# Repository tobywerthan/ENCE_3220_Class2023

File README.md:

# **ENCE_3220_Class2023 Phase D**
Phase D of ENCE-3220 tasked students to design a PCB using the STM32f407G and the STM32CubeIDE. A friend of mine recently asked me if I could design a device that would help him monitor the temperature in his bearded dragon's enclosure. This project seemed like the perfect opportunity to begin designing such a device.

## Project Requirements
The requirements for this temperature monitor aren't complex. The system must be able to read the current temperature, additional data is a plus. The system must also be able to display that data in a readable manner. The system must utilize the STM32F407G Discovery Board, and the software must be developed in the STM32CubeIDE. In summary, the system requirements are as follows: 
- Read temperature
- Display temperature in real time
- Utilize the STM32F407G Discovery Board
- Software developed in the STM32CubeIDE

## System Design
The design for this system includes the STM32F407G Discovery Board, an lcd display, and a temperature sensor. A block diagram of key components and their pin connections to the STM32F4. 

## Components Selection
Key components for this system include the LCD1602A display, the DHT11 temperature and humidity sensor, and the STM32F4 discovery board. A full list of the required components can be seen in the table below. 

| References  | Value       | Footprint   |
| :-----------: | :-----------: | :-----------: |
| U2 | DHT11 | Connector_PinSocket_2.54mm:PinSocket_1x03_P2.54mm_Vertical_SMD_Pin1Right |
| U1 | LCD1602A | Connector_PinSocket_2.54mm:PinSocket_1x16_P2.54mm_Vertical_SMD_Pin1Right |
| J1 & J2 | STM32F4 Discovery Board | 2x Connector_PinSocket_2.54mm:PinSocket_2x25_P2.54mm_Vertical |
| RV1 | 1000Ω | Connector_PinSocket_2.54mm:PinSocket_1x05_P2.54mm_Vertical_SMD_Pin1Right |
| R1 | 910Ω | Resistor_SMD:R_0603_1608Metric |
| C1 | 1mF | Capacitor_SMD:C_0603_1608Metric |

## Build Prototype

## STM32 Shield Design
The goal for this project was to develop a shield for the STM32F4 that implements the designed system. 

### Schematic
The schematic for this system contains three modules. The modules are categorized by component: "LCD1602A Pinout", "DHT11 Pinout", and "STM32 Discovery board Pinout". 

#### LCD Display

#### DHT11

#### STM32F4

### PCB
This shield was designed so that the componenets used during prototyping could be directly placed on the PCB using pin socket connectors instead of surface mounting components. The main concern when designing the PCB was to allocate enough space for the components once they are connected to the pin sockets. This was managed through some crude measurements as well as trial and error. 

#### KiCad

#### 3D Render

#### 3D Render with Components 

## Software Development
Both the LCD display and the temperature sensor require delays in units of microseconds in order to function correctly. Unfortunately, the delay provided by the HAL library has a minimum of 1 millisecond. To achieve a delay in microseconds, the following code is implemented in the library for both sensors:
```
void microDelay (uint16_t us)
{
	__HAL_TIM_SET_COUNTER(&timer, 0);
	while (__HAL_TIM_GET_COUNTER(&timer) < us);
}
```
The timers used for the micro delays are timer1 and timer2 sourced by the internal clock of the STM32. Both timers share a prescaler value of 83 and a counter period of 4095. The LCD library provided functions for clearing the display, moving the cursor on the display, and writing strings to the display. Every loop execution, the LCD displays the temperature on the top row, and then the humidity on the bottom row. The LCD needs to clear every loop execution as the values update, this forces the loop to implement a delay so that the value can display befor being cleared. Because the LCD displays requires a delay, the rate at which the temperature sensor is read needs to be faster than that delay. In this case, the delay for the lcd was 1 second. Therefore, a timer driven interrupt is implemented using timer6. This interrupt occurs every half second, which is plenty fast enough considering the display rate of the LCD display. Each time the interrupt occurs, the temperature and humidity values are read and stored. A flow chart of the program can be seen below:

## Future Iterations

While this project is practical, this kind of device already exists. A way to improve this design would be to use the ESP8266 microchip to send alerts to a certain device once the temperature has reached a specified threshold. Additionally, adding a UVB sensor would give the user more information about the enviornment. Powering the system with a battery would allow it to be portable. Because the device is meant to detect high temperatures and UVB, charging the battery through solar might not be a bad idea either.

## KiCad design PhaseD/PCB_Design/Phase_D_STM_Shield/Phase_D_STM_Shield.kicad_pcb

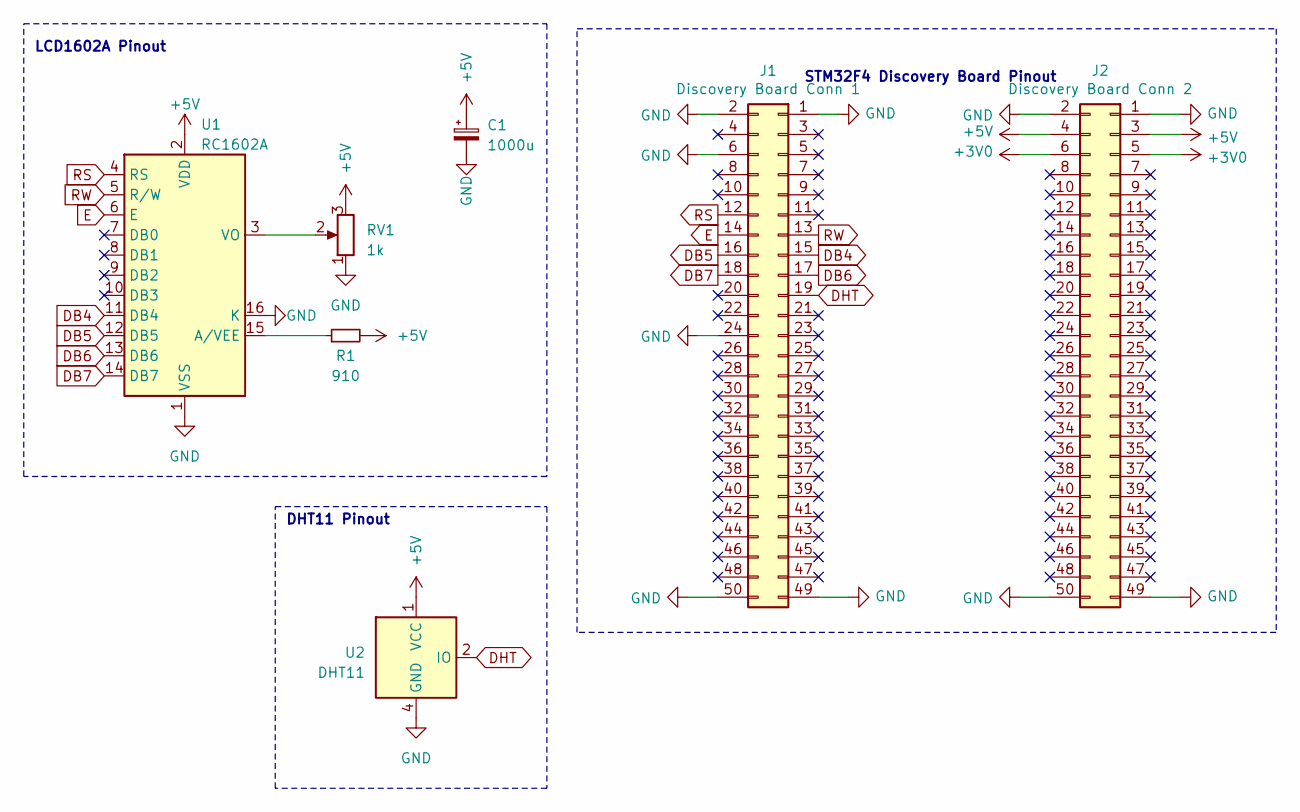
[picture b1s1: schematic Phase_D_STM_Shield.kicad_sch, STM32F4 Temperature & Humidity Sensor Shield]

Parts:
C1: 1000u; C_0603_1608Metric
J1: Discovery Board Conn 1; PinSocket_2x25_P2.54mm_Vertical
J2: Discovery Board Conn 2; PinSocket_2x25_P2.54mm_Vertical
R1: 910; R_0603_1608Metric
RV1: 1k; PinSocket_1x05_P2.54mm_Vertical_SMD_Pin1Right
U1: RC1602A; PinSocket_1x16_P2.54mm_Vertical_SMD_Pin1Right
U2: DHT11; PinSocket_1x03_P2.54mm_Vertical_SMD_Pin1Right

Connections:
+3V0: J2.5, J2.6
+5V: C1.1, J2.3, J2.4, R1.2, RV1.3, U1.2 (VDD), U2.1 (VCC)
DB4: J1.15, U1.11 (DB4)
DB5: J1.16, U1.12 (DB5)
DB6: J1.17, U1.13 (DB6)
DB7: J1.18, U1.14 (DB7)
DHT: J1.19, U2.2 (IO)
E: J1.14, U1.6 (E)
GND: C1.2, J1.1, J1.2, J1.6, J1.24, J1.49, J1.50, J2.1, J2.2, J2.49, J2.50, RV1.1, U1.1 (VSS), U1.16 (K), U2.4 (GND)
unnamed: R1.1, U1.15 (A/VEE)
unnamed: RV1.2, U1.3 (VO)
RS: J1.12, U1.4 (RS)
RW: J1.13, U1.5 (R/W)

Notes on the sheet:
STM32F4 Discovery Board Pinout
DHT11 Pinout
LCD1602A Pinout

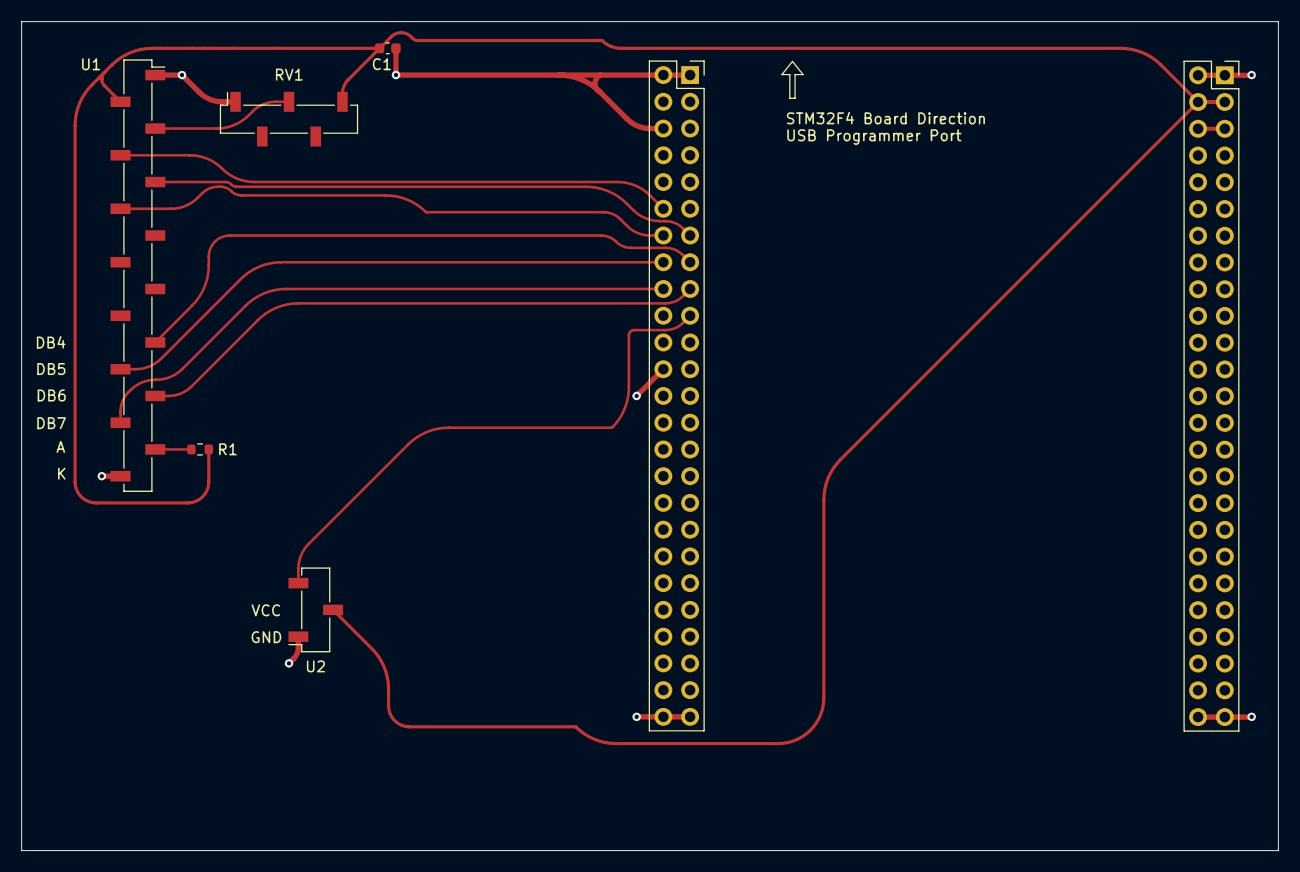
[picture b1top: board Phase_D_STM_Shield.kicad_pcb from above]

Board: 2 copper layers, 119.4 x 78.7 mm, 7 parts (0 on the bottom side), 13 nets.

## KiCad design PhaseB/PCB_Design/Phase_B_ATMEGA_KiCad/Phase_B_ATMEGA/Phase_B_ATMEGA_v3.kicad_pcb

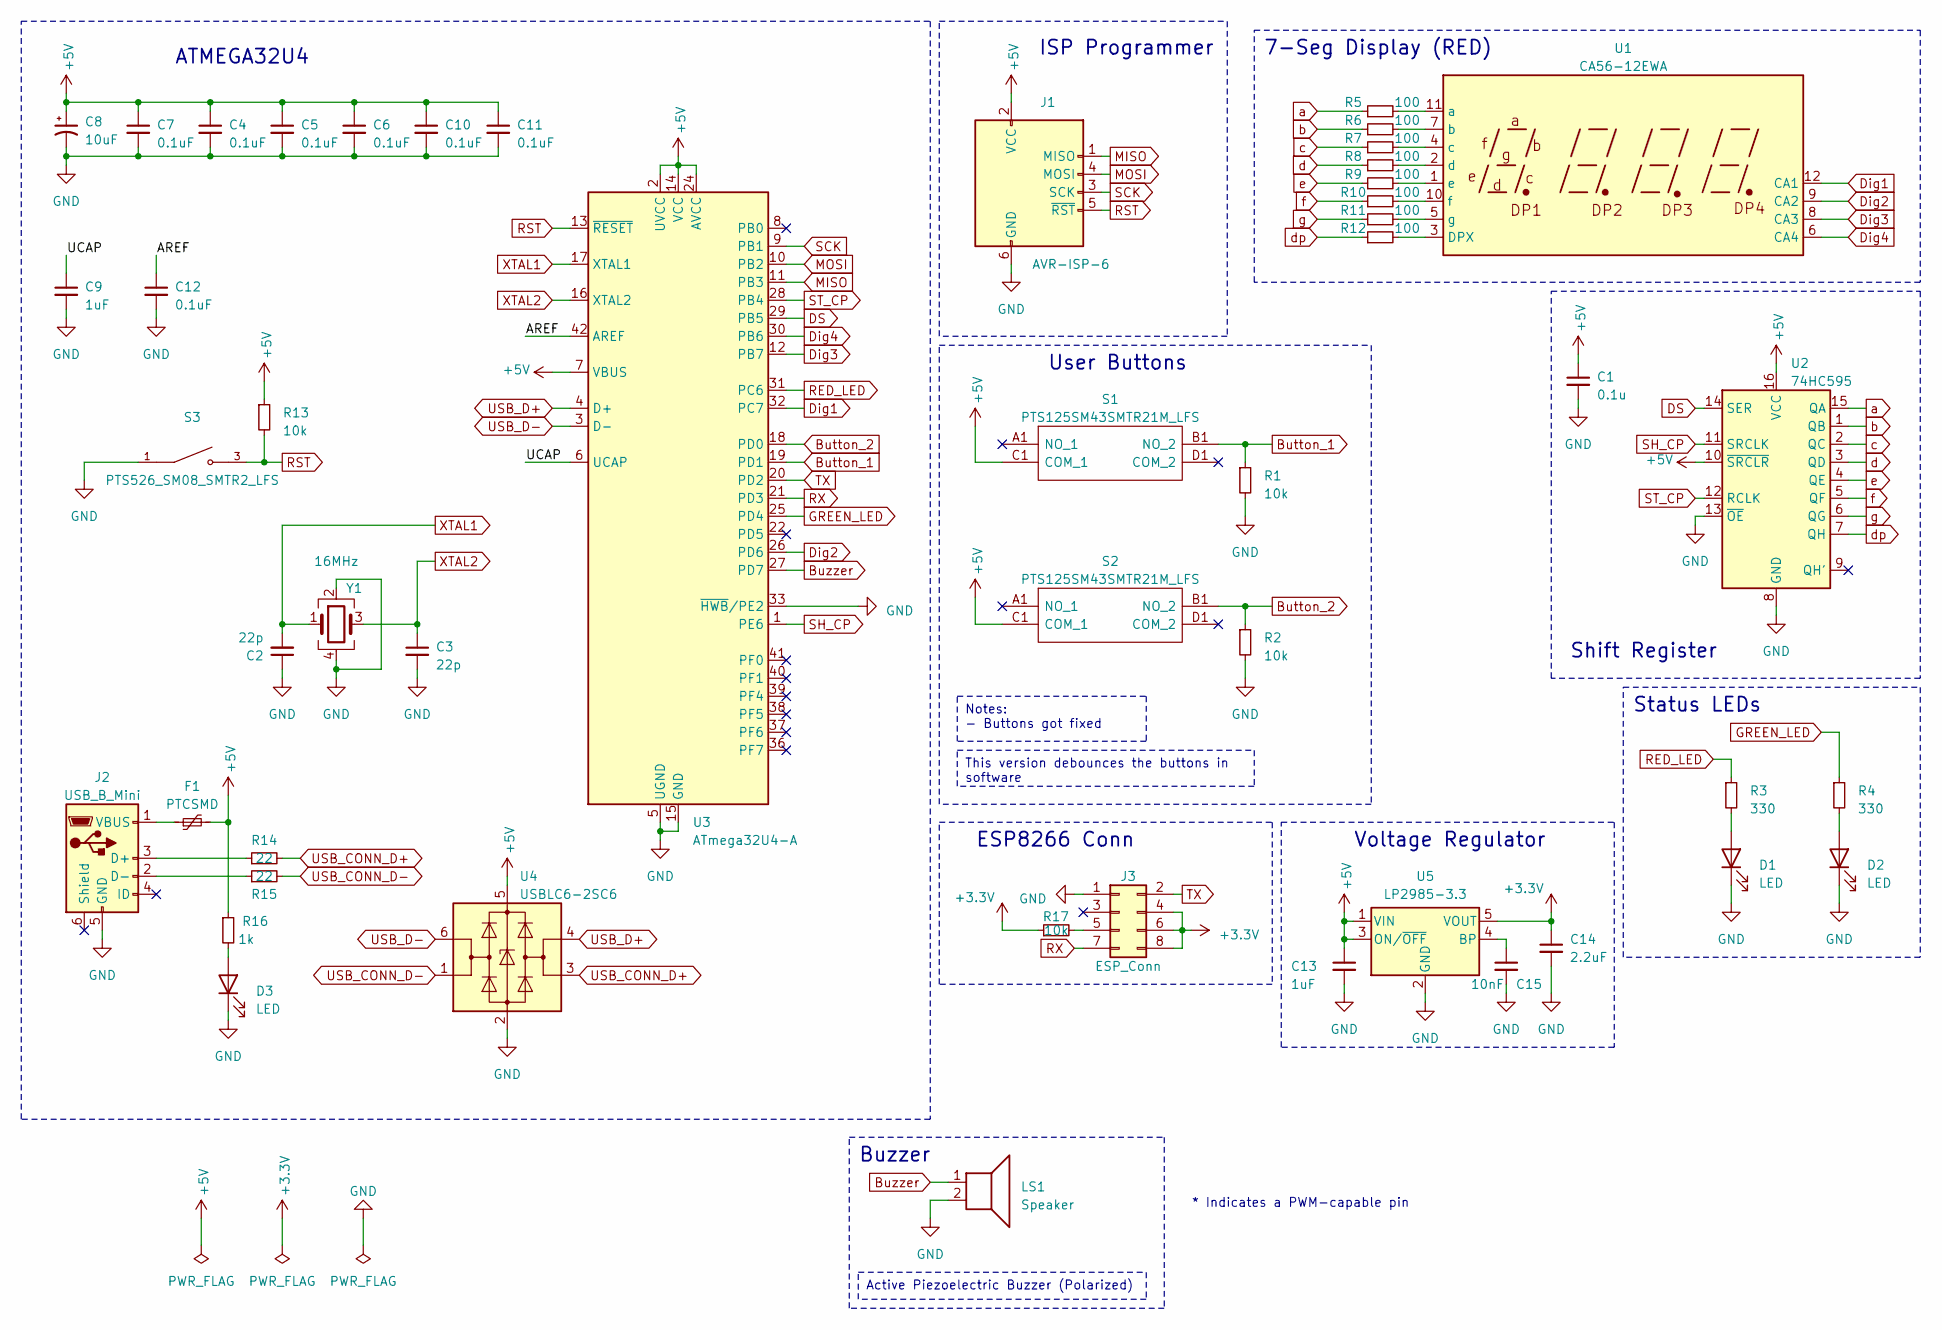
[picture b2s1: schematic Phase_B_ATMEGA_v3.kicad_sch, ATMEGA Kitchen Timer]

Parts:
C1: 0.1u; C_0603_1608Metric
C2, C3: 22p; C_0603_1608Metric
C4, C5, C6, C7, C10, C11, C12: 0.1uF; C_0603_1608Metric
C8: 10uF; C_0805_2012Metric
C9, C13: 1uF; C_0603_1608Metric
C14: 2.2uF; C_0603_1608Metric
C15: 10nF; C_0603_1608Metric
D1, D2, D3: LED; LED_0805_2012Metric
F1: PTCSMD; Fuse_1812_4532Metric
J1: AVR-ISP-6; PinSocket_2x03_P2.54mm_Vertical
J2: USB_B_Mini; USB_Mini-B_Lumberg_2486_01_Horizontal
J3: ESP_Conn; PinSocket_2x04_P2.54mm_Vertical
LS1: Speaker; Buzzer_12x9.5RM7.6
R1, R2: 10k; R_0805_2012Metric
R3, R4: 330; R_0805_2012Metric
R5, R6, R7, R8, R9, R10, R11, R12: 100; R_0805_2012Metric
R13, R17: 10k; R_0603_1608Metric
R14, R15: 22; R_0603_1608Metric
R16: 1k; R_0603_1608Metric
S1, S2: PTS125SM43SMTR21M_LFS; PTS125_SMD_Button; Manufacturer_Part_Number PTS125SM43SMTR21M LFS; Mouser Part Number 611-PTS125S43SMTRLFS
S3: PTS526_SM08_SMTR2_LFS; PTS526_SMD_Button; PARTREV 20 mar 19
U1: CA56-12EWA
U2: 74HC595; TSSOP-16_4.4x5mm_P0.65mm
U3: ATmega32U4-A; TQFP-44_10x10mm_P0.8mm
U4: USBLC6-2SC6; SOT-23-6
U5: LP2985-3.3; SOT-23-5
Y1: 16MHz; Crystal_SMD_Abracon_ABM8G-4Pin_3.2x2.5mm

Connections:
+3.3V: C14.1, J3.4, J3.6, J3.8, R17.1, U5.5 (VOUT)
+5V: C1.1, C4.1, C5.1, C6.1, C7.1, C8.1, C10.1, C11.1, C13.1, F1.2, J1.2 (VCC), R13.1, R16.1, S1.C1 (COM_1), S2.C1 (COM_1), U2.10 (~SRCLR), U2.16 (VCC), U3.2 (UVCC), U3.7 (VBUS), U3.14 (VCC), U3.24 (AVCC), U3.34 (VCC), U3.44 (AVCC), U4.5 (VBUS), U5.1 (VIN), U5.3 (ON/~OFF)
/AREF: C12.1, U3.42 (AREF)
/UCAP: C9.1, U3.6 (UCAP)
Button_1: R1.1, S1.B1 (NO_2), U3.19 (PD1)
Button_2: R2.1, S2.B1 (NO_2), U3.18 (PD0)
Buzzer: LS1.1, U3.27 (PD7)
DS: U2.14 (SER), U3.29 (PB5)
Dig1: U1.12 (CA1), U3.32 (PC7)
Dig2: U1.9 (CA2), U3.26 (PD6)
Dig3: U1.8 (CA3), U3.12 (PB7)
Dig4: U1.6 (CA4), U3.30 (PB6)
GND: C1.2, C2.1, C3.2, C4.2, C5.2, C6.2, C7.2, C8.2, C9.2, C10.2, C11.2, C12.2, C13.2, C14.2, C15.2, D1.1 (K), D2.1 (K), D3.1 (K), J1.6 (GND), J2.5 (GND), J3.1, LS1.2, R1.2, R2.2, S3.1, U2.8 (GND), U2.13 (~OE), U3.5 (UGND), U3.15 (GND), U3.23 (GND), U3.33 (~HWB/PE2), U3.35 (GND), U3.43 (GND), U4.2 (GND), U5.2 (GND), Y1.2, Y1.4
GREEN_LED: R4.1, U3.25 (PD4)
MISO: J1.1 (MISO), U3.11 (PB3)
MOSI: J1.4 (MOSI), U3.10 (PB2)
unnamed: D1.2 (A), R3.2
unnamed: D2.2 (A), R4.2
unnamed: D3.2 (A), R16.2
unnamed: J2.3 (D+), R14.1
unnamed: J2.2 (D-), R15.1
unnamed: F1.1, J2.1 (VBUS)
unnamed: J3.5, R17.2
unnamed: R12.2, U1.3 (DPX)
unnamed: R5.2, U1.11 (a)
unnamed: R6.2, U1.7 (b)
unnamed: R7.2, U1.4 (c)
unnamed: R8.2, U1.2 (d)
unnamed: R9.2, U1.1 (e)
unnamed: R10.2, U1.10 (f)
unnamed: R11.2, U1.5 (g)
unnamed: C15.1, U5.4 (BP)
RED_LED: R3.1, U3.31 (PC6)
RST: J1.5 (~RST), R13.2, S3.3, U3.13 (~RESET)
RX: J3.7, U3.21 (PD3)
SCK: J1.3 (SCK), U3.9 (PB1)
SH_CP: U2.11 (SRCLK), U3.1 (PE6)
ST_CP: U2.12 (RCLK), U3.28 (PB4)
TX: J3.2, U3.20 (PD2)
USB_CONN_D+: R14.2, U4.3 (I/O2)
USB_CONN_D-: R15.2, U4.1 (I/O1)
USB_D+: U3.4 (D+), U4.4 (I/O2)
USB_D-: U3.3 (D-), U4.6 (I/O1)
XTAL1: C2.2, U3.17 (XTAL1), Y1.1
XTAL2: C3.1, U3.16 (XTAL2), Y1.3
a: R5.1, U2.15 (QA)
b: R6.1, U2.1 (QB)
c: R7.1, U2.2 (QC)
d: R8.1, U2.3 (QD)
dp: R12.1, U2.7 (QH)
e: R9.1, U2.4 (QE)
f: R10.1, U2.5 (QF)
g: R11.1, U2.6 (QG)

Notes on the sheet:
Notes: - Buttons got fixed
Active Piezoelectric Buzzer (Polarized)
This version debounces the buttons in software
Shift Register
Voltage Regulator
Status LEDs
ATMEGA32U4
User Buttons
Buzzer
* Indicates a PWM-capable pin
7-Seg Display (RED)
ISP Programmer
ESP8266 Conn

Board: 2 copper layers, 53 parts (0 on the bottom side), 53 nets, no tracks yet.

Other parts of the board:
M3, M3#2, M3#3, M3#4: MountingHole_3.2mm_M3

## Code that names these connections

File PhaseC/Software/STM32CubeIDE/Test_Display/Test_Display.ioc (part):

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Mcu.Name=STM32F407V(E-G)Tx
Mcu.Package=LQFP100
Mcu.UserName=STM32F407VGTx
PA0-WKUP.GPIOParameters=GPIO_PuPd,GPIO_Label,GPIO_ModeDefaultEXTI
PA0-WKUP.GPIO_Label=B1 [Blue PushButton]
PA0-WKUP.GPIO_ModeDefaultEXTI=GPIO_MODE_IT_RISING
PA0-WKUP.GPIO_PuPd=GPIO_NOPULL
PA0-WKUP.Signal=GPXTI0
PA10.GPIOParameters=GPIO_Speed,GPIO_PuPd,GPIO_Label,GPIO_Mode
PA10.GPIO_Label=OTG_FS_ID
PA10.GPIO_Mode=GPIO_MODE_AF_PP
PA10.GPIO_PuPd=GPIO_NOPULL
PA10.GPIO_Speed=GPIO_SPEED_FREQ_LOW
PA10.Signal=USB_OTG_FS_ID
PA11.GPIOParameters=GPIO_Speed,GPIO_PuPd,GPIO_Label,GPIO_Mode
PA11.GPIO_Label=OTG_FS_DM
PA11.GPIO_Mode=GPIO_MODE_AF_PP
PA11.GPIO_PuPd=GPIO_NOPULL
PA11.GPIO_Speed=GPIO_SPEED_FREQ_LOW
PA11.Signal=USB_OTG_FS_DM
PA12.GPIOParameters=GPIO_Speed,GPIO_PuPd,GPIO_Label,GPIO_Mode
PA12.GPIO_Label=OTG_FS_DP
PA12.GPIO_Mode=GPIO_MODE_AF_PP
PA12.GPIO_PuPd=GPIO_NOPULL
PA12.GPIO_Speed=GPIO_SPEED_FREQ_LOW
PA12.Signal=USB_OTG_FS_DP
PA13.GPIOParameters=GPIO_Label
PA13.GPIO_Label=SWDIO
PA13.Mode=Serial_Wire
PA13.Signal=SYS_JTMS-SWDIO
PA14.GPIOParameters=GPIO_Label
PA14.GPIO_Label=SWCLK
PA14.Mode=Serial_Wire
PA14.Signal=SYS_JTCK-SWCLK
PA4.GPIOParameters=GPIO_Speed,GPIO_PuPd,GPIO_Label,GPIO_Mode
PA4.GPIO_Label=I2S3_WS [CS43L22_LRCK]
PA4.GPIO_Mode=GPIO_MODE_AF_PP
PA4.GPIO_PuPd=GPIO_NOPULL
PA4.GPIO_Speed=GPIO_SPEED_FREQ_LOW
PA4.Signal=I2S3_WS
PA5.GPIOParameters=GPIO_Speed,GPIO_PuPd,GPIO_Label,GPIO_Mode
PA5.GPIO_Label=SPI1_SCK [LIS302DL_SCL/SPC]
PA5.GPIO_Mode=GPIO_MODE_AF_PP
PA5.GPIO_PuPd=GPIO_NOPULL
PA5.GPIO_Speed=GPIO_SPEED_FREQ_LOW
PA5.Signal=SPI1_SCK
PA6.GPIOParameters=GPIO_Speed,GPIO_PuPd,GPIO_Label,GPIO_Mode
PA6.GPIO_Label=SPI1_MISO [LIS302DL_SDO]
PA6.GPIO_Mode=GPIO_MODE_AF_PP
PA6.GPIO_PuPd=GPIO_NOPULL
PA6.GPIO_Speed=GPIO_SPEED_FREQ_LOW
PA6.Signal=SPI1_MISO
PA7.GPIOParameters=GPIO_Speed,GPIO_PuPd,GPIO_Label,GPIO_Mode
PA7.GPIO_Label=SPI1_MOSI [LIS302DL_SDA/SDI/SDO]
PA7.GPIO_Mode=GPIO_MODE_AF_PP
PA7.GPIO_PuPd=GPIO_NOPULL
PA7.GPIO_Speed=GPIO_SPEED_FREQ_LOW
PA7.Signal=SPI1_MOSI
PA9.GPIOParameters=GPIO_PuPd,GPIO_Label,GPIO_Mode
PA9.GPIO_Label=VBUS_FS
PA9.GPIO_Mode=GPIO_MODE_INPUT
PA9.GPIO_PuPd=GPIO_NOPULL
PA9.Signal=USB_OTG_FS_VBUS
PB0.GPIOParameters=GPIO_Label
PB0.GPIO_Label=GREEN_LED
PB0.Signal=GPIO_Output
PB1.GPIOParameters=GPIO_Label
PB1.GPIO_Label=RED_LED
PB1.Signal=GPIO_Output
PB10.GPIOParameters=GPIO_Speed,GPIO_PuPd,GPIO_Label,GPIO_Mode
PB10.GPIO_Label=CLK_IN [MP45DT02_CLK]
PB10.GPIO_Mode=GPIO_MODE_AF_PP
PB10.GPIO_PuPd=GPIO_NOPULL
PB10.GPIO_Speed=GPIO_SPEED_FREQ_LOW
PB10.Signal=I2S2_CK
PB2.GPIOParameters=GPIO_PuPd,GPIO_Label,GPIO_Mode
PB2.GPIO_Label=BOOT1
PB2.GPIO_Mode=GPIO_MODE_INPUT
PB2.GPIO_PuPd=GPIO_NOPULL
PB2.Signal=GPIO_Input
PB3.GPIOParameters=GPIO_Label
PB3.GPIO_Label=SWO
PB3.Signal=SYS_JTDO-SWO
PB4.GPIOParameters=GPIO_Label
PB4.GPIO_Label=DIGIT_1
PB4.Signal=GPIO_Output
PB5.GPIOParameters=GPIO_Label
PB5.GPIO_Label=DIGIT_2
PB5.Signal=GPIO_Output
PB6.GPIOParameters=GPIO_Speed,GPIO_PuPd,GPIO_Label,GPIO_Pu,GPIO_Mode
PB6.GPIO_Label=Audio_SCL [CS43L22_SCL]
PB6.GPIO_Mode=GPIO_MODE_AF_OD
PB6.GPIO_Pu=GPIO_PULLUP
PB6.GPIO_PuPd=GPIO_NOPULL
PB6.GPIO_Speed=GPIO_SPEED_FREQ_LOW
PB6.Signal=I2C1_SCL
PB7.GPIOParameters=GPIO_Label
PB7.GPIO_Label=DIGIT_3
PB7.Signal=GPIO_Output
PB8.GPIOParameters=GPIO_Label
PB8.GPIO_Label=DIGIT_4
PB8.Signal=GPIO_Output
PB9.GPIOParameters=GPIO_Speed,GPIO_PuPd,GPIO_Label,GPIO_Pu,GPIO_Mode
PB9.GPIO_Label=Audio_SDA [CS43L22_SDA]
PB9.GPIO_Mode=GPIO_MODE_AF_OD
PB9.GPIO_Pu=GPIO_PULLUP
PB9.GPIO_PuPd=GPIO_NOPULL
PB9.GPIO_Speed=GPIO_SPEED_FREQ_LOW
PB9.Signal=I2C1_SDA
PC0.GPIOParameters=GPIO_Speed,PinState,GPIO_PuPd,GPIO_Label
PC0.GPIO_Label=OTG_FS_PowerSwitchOn
PC0.GPIO_PuPd=GPIO_NOPULL
PC0.GPIO_Speed=GPIO_SPEED_FREQ_LOW
PC0.PinState=GPIO_PIN_SET
PC0.Signal=GPIO_Output
PC10.GPIOParameters=GPIO_Speed,GPIO_PuPd,GPIO_Label,GPIO_Mode
PC10.GPIO_Label=I2S3_SCK [CS43L22_SCLK]
PC10.GPIO_Mode=GPIO_MODE_AF_PP
PC10.GPIO_PuPd=GPIO_NOPULL
PC10.GPIO_Speed=GPIO_SPEED_FREQ_LOW
PC10.Signal=I2S3_CK
PC12.GPIOParameters=GPIO_Speed,GPIO_PuPd,GPIO_Label,GPIO_Mode
PC12.GPIO_Label=I2S3_SD [CS43L22_SDIN]
PC12.GPIO_Mode=GPIO_MODE_AF_PP
PC12.GPIO_PuPd=GPIO_NOPULL
PC12.GPIO_Speed=GPIO_SPEED_FREQ_LOW
PC12.Signal=I2S3_SD
PC14-OSC32_IN.GPIOParameters=GPIO_Label
PC14-OSC32_IN.GPIO_Label=PC14-OSC32_IN
PC14-OSC32_IN.Mode=LSE-External-Oscillator
PC14-OSC32_IN.Signal=RCC_OSC32_IN
PC15-OSC32_OUT.GPIOParameters=GPIO_Label
PC15-OSC32_OUT.GPIO_Label=PC15-OSC32_OUT
PC15-OSC32_OUT.Mode=LSE-External-Oscillator
PC15-OSC32_OUT.Signal=RCC_OSC32_OUT
PC3.GPIOParameters=GPIO_Speed,GPIO_PuPd,GPIO_Label,GPIO_Mode
PC3.GPIO_Label=PDM_OUT [MP45DT02_DOUT]
PC3.GPIO_Mode=GPIO_MODE_AF_PP
PC3.GPIO_PuPd=GPIO_NOPULL
PC3.GPIO_Speed=GPIO_SPEED_FREQ_LOW
PC3.Signal=I2S2_SD
PC4.GPIOParameters=GPIO_Label
PC4.GPIO_Label=BUTTON_1
PC4.Signal=GPXTI4
PC5.GPIOParameters=GPIO_Label
PC5.GPIO_Label=BUTTON_2
PC5.Signal=GPXTI5
PC7.GPIOParameters=GPIO_Speed,GPIO_PuPd,GPIO_Label,GPIO_Mode
PC7.GPIO_Label=I2S3_MCK [CS43L22_MCLK]
PC7.GPIO_Mode=GPIO_MODE_AF_PP
PC7.GPIO_PuPd=GPIO_NOPULL
PC7.GPIO_Speed=GPIO_SPEED_FREQ_LOW
PC7.Signal=I2S3_MCK
PD1.GPIOParameters=GPIO_Label
PD1.GPIO_Label=DS
PD1.Signal=GPIO_Output
PD12.GPIOParameters=GPIO_Speed,GPIO_PuPd,GPIO_Label
PD12.GPIO_Label=LD4 [Green Led]
PD12.GPIO_PuPd=GPIO_NOPULL
PD12.GPIO_Speed=GPIO_SPEED_FREQ_LOW
PD12.Signal=GPIO_Output
PD13.GPIOParameters=GPIO_Speed,GPIO_PuPd,GPIO_Label
PD13.GPIO_Label=LD3 [Orange Led]
PD13.GPIO_PuPd=GPIO_NOPULL
PD13.GPIO_Speed=GPIO_SPEED_FREQ_LOW
PD13.Signal=GPIO_Output
PD14.GPIOParameters=GPIO_Speed,GPIO_PuPd,GPIO_Label
PD14.GPIO_Label=LD5 [Red Led]
PD14.GPIO_PuPd=GPIO_NOPULL
PD14.GPIO_Speed=GPIO_SPEED_FREQ_LOW
PD14.Signal=GPIO_Output
PD15.GPIOParameters=GPIO_Speed,GPIO_PuPd,GPIO_Label
PD15.GPIO_Label=LD6 [Blue Led]
PD15.GPIO_PuPd=GPIO_NOPULL
PD15.GPIO_Speed=GPIO_SPEED_FREQ_LOW
PD15.Signal=GPIO_Output
PD2.GPIOParameters=GPIO_Label
PD2.GPIO_Label=ST_CP
PD2.Signal=GPIO_Output
PD3.GPIOParameters=GPIO_Label
PD3.GPIO_Label=SH_CP
PD3.Signal=GPIO_Output
PD4.GPIOParameters=GPIO_Speed,GPIO_PuPd,GPIO_Label
PD4.GPIO_Label=Audio_RST [CS43L22_RESET]
PD4.GPIO_PuPd=GPIO_NOPULL
PD4.GPIO_Speed=GPIO_SPEED_FREQ_LOW
PD4.Signal=GPIO_Output
PD5.GPIOParameters=GPIO_PuPd,GPIO_Label,GPIO_Mode
PD5.GPIO_Label=OTG_FS_OverCurrent
PD5.GPIO_Mode=GPIO_MODE_INPUT
PD5.GPIO_PuPd=GPIO_NOPULL
PD5.Signal=GPIO_Input
PE1.GPIOParameters=GPIO_PuPd,GPIO_Label,GPIO_ModeDefaultEXTI
PE1.GPIO_Label=MEMS_INT2 [LIS302DL_INT2]
PE1.GPIO_ModeDefaultEXTI=GPIO_MODE_EVT_RISING
PE1.GPIO_PuPd=GPIO_NOPULL
PE1.Signal=GPXTI1
PE3.GPIOParameters=GPIO_Speed,GPIO_PuPd,GPIO_Label
PE3.GPIO_Label=CS_I2C/SPI [LIS302DL_CS_I2C/SPI]
PE3.GPIO_PuPd=GPIO_NOPULL
PE3.GPIO_Speed=GPIO_SPEED_FREQ_LOW
PE3.Signal=GPIO_Output
PH0-OSC_IN.GPIOParameters=GPIO_Label
PH0-OSC_IN.GPIO_Label=PH0-OSC_IN
PH0-OSC_IN.Mode=HSE-External-Oscillator
PH0-OSC_IN.Signal=RCC_OSC_IN
PH1-OSC_OUT.GPIOParameters=GPIO_Label
PH1-OSC_OUT.GPIO_Label=PH1-OSC_OUT
PH1-OSC_OUT.Mode=HSE-External-Oscillator
PH1-OSC_OUT.Signal=RCC_OSC_OUT
RCC.HSE_VALUE=8000000
RCC.SYSCLKFreq_VALUE=168000000
RCC.SYSCLKSource=RCC_SYSCLKSOURCE_PLLCLK
board=STM32F407G-DISC1
boardIOC=true

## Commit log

2023-04-06 Initial file structure and PhaseA arduino code
2023-04-11 Added PCB design and Arduino code
    The KiCad files were added underneath PCB_Design and the Arduino code was added underneath Arduino_Code.
2023-04-12 Phase A changes and Phase B addition
    Changes to PCB design and Arduino code comments in Phase A. Added the work in progress PCB design in Phase B.
2023-04-13 Added Notes
    Added various notes obtained through the design process of the PCB and software. The "proof_of_concept_prototype_board.png" and the "pcb_manufactured.png" were provided by Dr. Goncalo Martins.
2023-04-18 Phase_B PCB Layout design
    Component layout implemented and casing for the pcb was created
2023-04-18 updated step
2023-04-18 added .obj files
2023-04-18 moved 3d models and dxf to notes
2023-04-20 Phase_B_Final_Design
2023-04-20 file cleanup
2023-05-04 additions
2023-05-05 phase c and phase b report
2023-05-05 updated report
2023-05-31 PhaseD
2023-06-01 added gif
2023-06-07 updated phase b
2023-06-13 updated phase b phase b update
